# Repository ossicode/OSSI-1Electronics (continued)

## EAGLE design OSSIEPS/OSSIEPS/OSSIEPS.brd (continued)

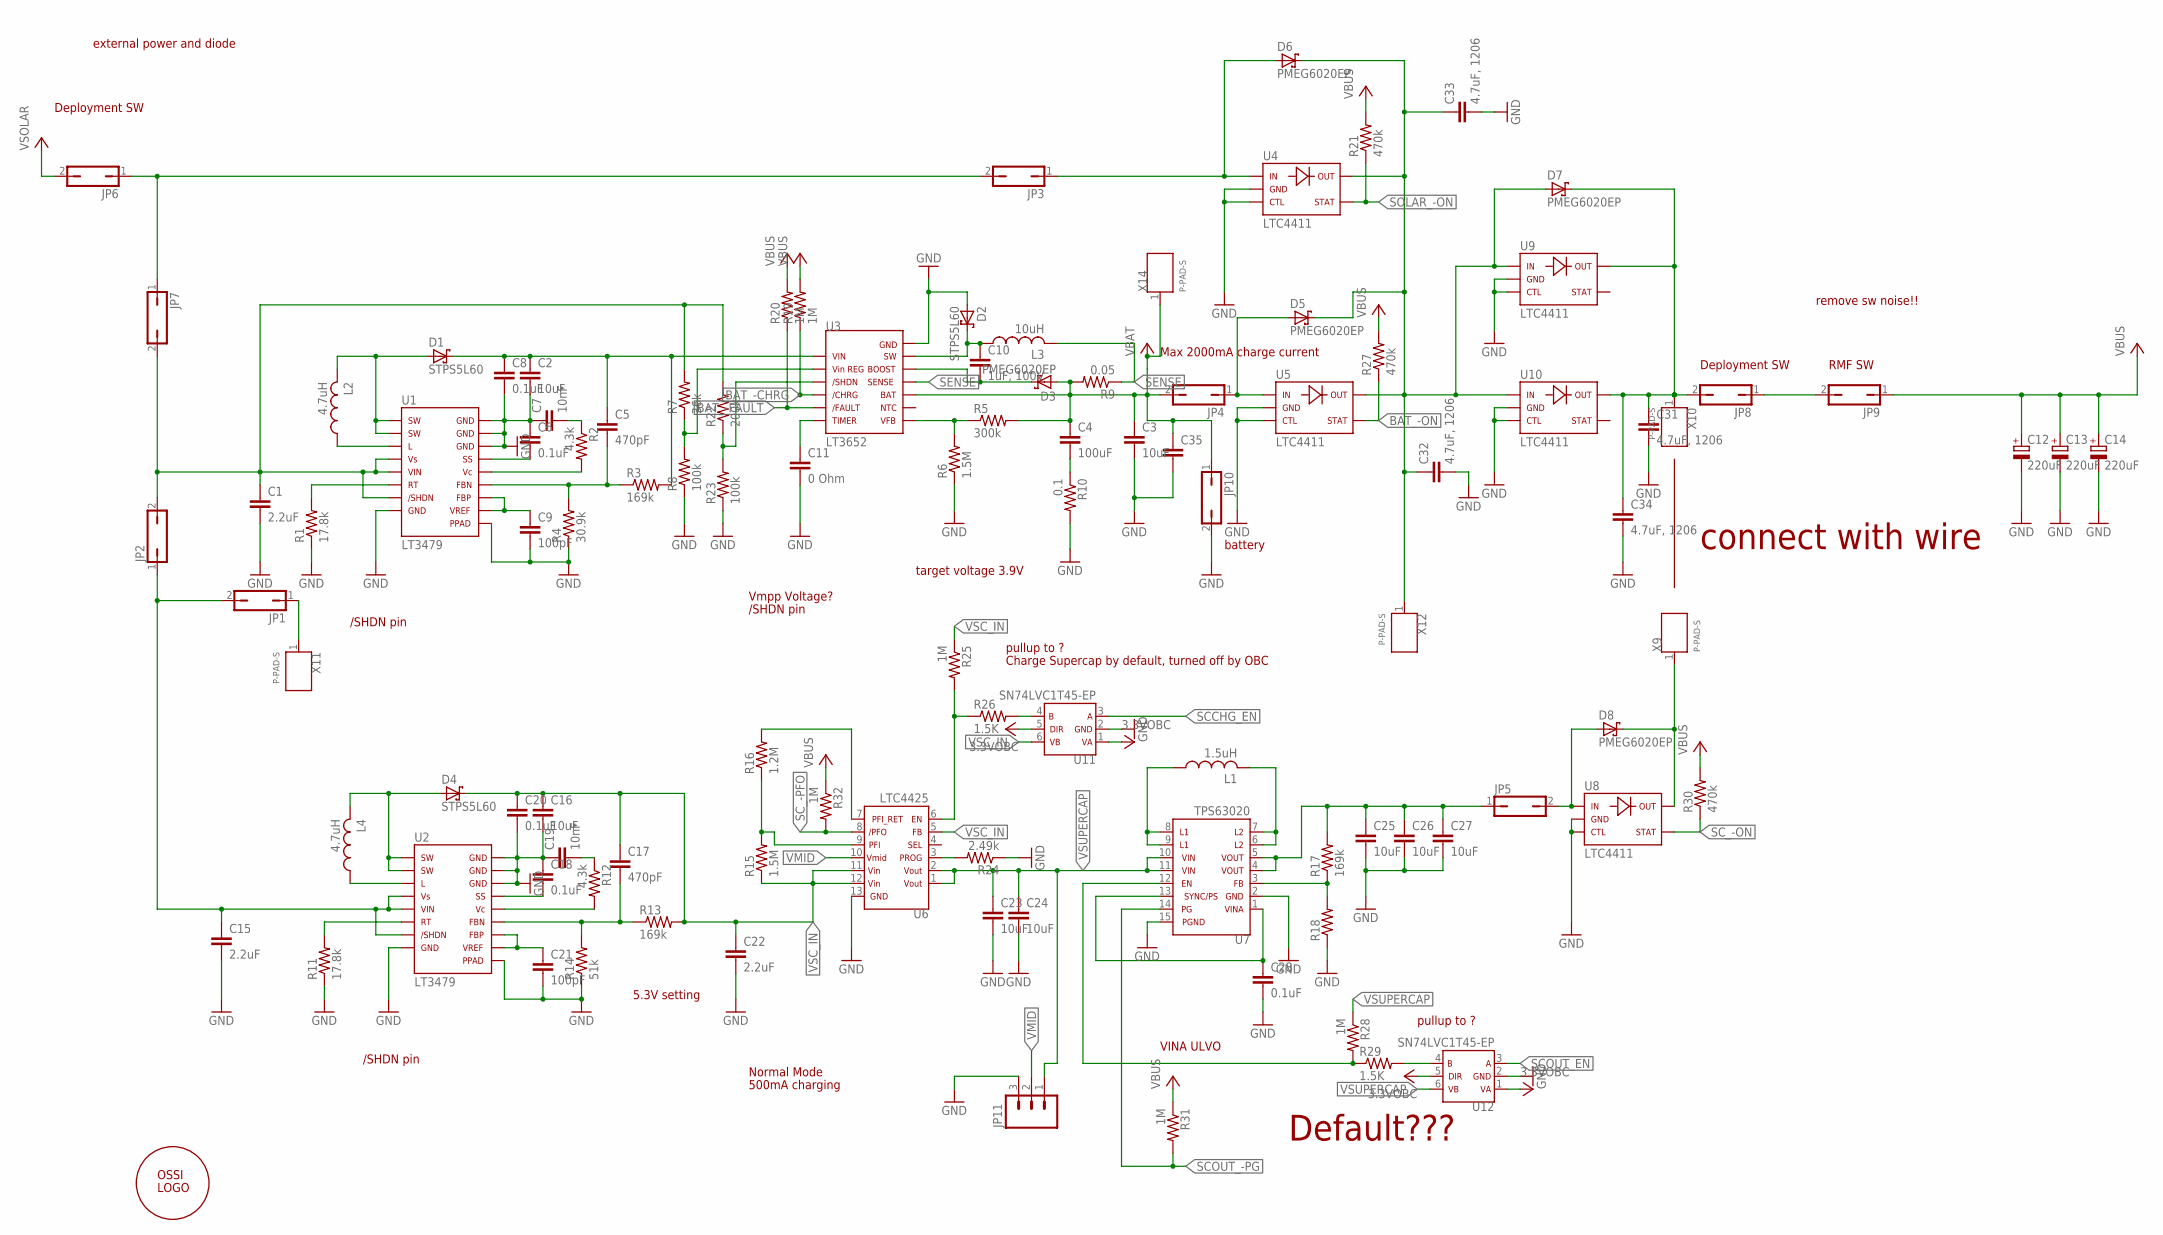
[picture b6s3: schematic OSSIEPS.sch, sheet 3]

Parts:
C1, C15, C22: 2.2uF; C1206-GCM31
C2, C3, C16, C23, C24, C25, C26, C27: 10uF; C1210-GCM32
C4: 100uF; C1210-TMK325
C5, C17: 470pF; C0603(1608)
C6, C8, C18, C20, C28: 0.1uF; C0603(1608)
C7, C19: 10nF; C0603(1608)
C9, C21: 100pF; C0603(1608)
C10: 1uF, 100V; C0805(2012)
C11: 0 Ohm; C0603(1608)
C12, C13, C14: 220uF; C2917(7343)-Y
C31, C32, C33, C34: 4.7uF, 1206; C1206-GCM31
C35: C0603(1608)
D1, D2, D4: STPS5L60
D3, D5, D6, D7, D8: PMEG6020EP
JP1, JP2, JP3, JP4, JP5, JP6, JP7, JP8, JP9, JP10: JP1Q; JP1
JP11: M03POLAR; MOLEX-1X3
L1: 1.5uH; L(4040)
L2, L4: 4.7uH; RLF7030
L3: 10uH; RLF12545
R1, R11: 17.8k; R0603(1608)
R2, R12: 4.3k; R0603(1608)
R3, R13, R17: 169k; R0603(1608)
R4: 30.9k; R0603(1608)
R5: 300k; R0603(1608)
R6, R15: 1.5M; R0603(1608)
R7: 36k; R0603(1608)
R8, R23: 100k; R0603(1608)
R9: 0.05; WSL1206
R10: 0.1; WSL1206
R14: 51k; R0603(1608)
R16: 1.2M; R0603(1608)
R18: R0603(1608)
R19, R20, R25, R28, R31, R32: 1M; R0603(1608)
R21, R27, R30: 470k; R0603(1608)
R22: 200k; R0603(1608)
R24: 2.49k; R0603(1608)
R26, R29: 1.5K; R0603(1608)
U1, U2: LT3479; TSSOP16-FE
U3: LT3652; MSE
U4, U5, U8, U9, U10: LTC4411; TSOT23-5
U6: LTC4425; MSE
U7: TPS63020; VSON-14
U11, U12: SN74LVC1T45-EP; SOT-6DCK
U$1: OSSILOGORECT; OSSILOGORECT1005
X9, X10, X11, X12, X14: P-PAD-S

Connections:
3.3VOBC: U11.1, U11.5, U12.1, U12.5; also elsewhere on the board
BAT_-CHRG: R19.1, U3.4; also elsewhere on the board
BAT_-FAULT: R20.1, U3.5; also elsewhere on the board
BAT_-ON: R27.1, U5.P$4; also elsewhere on the board
GND: C1.P$2 (2), C2.P$2 (2), C3.P$2 (2), C6.1, C7.1, C8.2, C9.2, C11.2, C12.2 (-), C13.2 (-), C14.2 (-), C15.P$2 (2), C16.P$2 (2), C18.1, C19.1, C20.2, C21.2, C22.P$2 (2), C23.P$2 (2), C24.P$2 (2), C25.P$2 (2), C26.P$2 (2), C27.P$2 (2), C28.2, C31.P$2 (2), C32.P$2 (2), C33.P$2 (2), C34.P$2 (2), C35.2, D2.A, JP10.2, JP11.3, R1.1, R4.1, R6.1, R8.1, R10.P$2 (2), R11.1, R14.1, R18.1, R23.1, R24.1, U1.8, U1.14, U1.15, U1.16, U1.PPAD, U2.8, U2.14, U2.15, U2.16, U2.PPAD, U3.13, U4.P$2, U4.P$3, U5.P$2, U5.P$3, U6.13, U7.2 (GND), U7.15 (PGND), U8.P$2, U8.P$3, U9.P$2, U9.P$3, U10.P$2, U10.P$3, U11.2, U12.2; also elsewhere on the board
unnamed: L2.P$1 (1), U1.3
unnamed: R7.1, R8.2, U3.2
unnamed: C2.P$1 (1), C5.1, C8.1, D1.C, R3.2, U3.1
unnamed: C4.P$2 (2), R10.P$1 (1)
unnamed: C6.2, U1.13
unnamed: D1.A, L2.P$2 (2), U1.1, U1.2
unnamed: C7.2, R2.1
unnamed: R2.2, U1.12
unnamed: C5.2, R3.1, R4.2, U1.11
unnamed: C9.1, U1.9, U1.10
unnamed: R1.2, U1.6
unnamed: R22.1, R23.2, U3.3
unnamed: C10.2, D3.C, U3.11
unnamed: D8.C, U8.P$5, X9.1
unnamed: L4.P$1 (1), U2.3
unnamed: C10.1, D2.C, L3.P$1 (1), U3.12
unnamed: R5.1, R6.2, U3.7
unnamed: C32.P$1 (1), C33.P$1 (1), D5.C, D6.C, D7.A, U4.P$5, U5.P$5, U9.P$1, U10.P$1, X12.1
unnamed: C11.1, U3.6
unnamed: R26.2, U11.4
unnamed: C18.2, U2.13
unnamed: D4.A, L4.P$2 (2), U2.1, U2.2
unnamed: C19.2, R12.1
unnamed: R12.2, U2.12
unnamed: C17.2, R13.1, R14.2, U2.11
unnamed: C21.1, U2.9, U2.10
unnamed: R11.2, U2.6
unnamed: C15.P$1 (1), JP1.2, JP2.1, U2.4, U2.5, U2.7
unnamed: R15.2, R16.1, U6.9
unnamed: L1.1, U7.8 (L1), U7.9 (L1_2)
unnamed: R16.2, U6.7
unnamed: L1.2, U7.6 (L2), U7.7 (L2_2)
unnamed: C25.P$1 (1), C26.P$1 (1), C27.P$1 (1), JP5.1, R17.2, U7.4 (VOUT), U7.5 (VOUT2)
unnamed: R17.1, R18.2, U7.3 (FB)
unnamed: C28.1, U7.1 (VINA), U7.13 (SYNC/PS)
unnamed: D6.A, JP3.1, U4.P$1
unnamed: R24.2, U6.3
unnamed: R28.2, R29.1, U7.12 (EN)
unnamed: D5.A, JP4.1, U5.P$1
unnamed: D8.A, JP5.2, U8.P$1
unnamed: C1.P$1 (1), JP2.2, JP7.2, R7.2, R22.2, U1.4, U1.5, U1.7
unnamed: R25.2, R26.1, U6.6
unnamed: JP3.2, JP6.1, JP7.1
unnamed: C31.P$1 (1), C34.P$1 (1), D7.C, JP8.2, U9.P$5, U10.P$5, X10.1
unnamed: R29.2, U12.4
unnamed: JP8.1, JP9.2
unnamed: JP1.1, X11.1
SCCHG_EN: U11.3; also elsewhere on the board
SCOUT_-PG: R31.2, U7.14 (PG); also elsewhere on the board
SCOUT_EN: U12.3; also elsewhere on the board
SC_-ON: R30.1, U8.P$4; also elsewhere on the board
SC_-PFO: R32.2, U6.8; also elsewhere on the board
SENSE: L3.P$2 (2), R9.P$1 (1), U3.10
SOLAR_-ON: R21.1, U4.P$4; also elsewhere on the board
VBAT: C3.P$1 (1), C4.P$1 (1), C35.1, D3.A, JP4.2, JP10.1, R5.2, R9.P$2 (2), U3.9, X14.1; also elsewhere on the board
VBUS: C12.1 (+), C13.1 (+), C14.1 (+), JP9.1, R19.2, R20.2, R21.2, R27.2, R30.2, R31.1, R32.1; also elsewhere on the board
VMID: JP11.2, U6.10
VSC_IN: C16.P$1 (1), C17.1, C20.1, C22.P$1 (1), D4.C, R13.2, R15.1, R25.1, U6.5, U6.11, U6.12, U11.6
VSOLAR: JP6.2; also elsewhere on the board
VSUPERCAP: C23.P$1 (1), C24.P$1 (1), JP11.1, R28.1, U6.1, U6.2, U7.10 (VIN), U7.11 (VIN2), U12.6; also elsewhere on the board

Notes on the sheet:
/SHDN pin
5.3V setting
VINA ULVO
Normal Mode
500mA charging
Charge Supercap by default, turned off by OBC
Vmpp Voltage?
Max 2000mA charge current
target voltage 3.9V
Deployment SW
RMF SW
external power and diode
pullup to ?
remove sw noise!!
battery
Default???
connect with wire

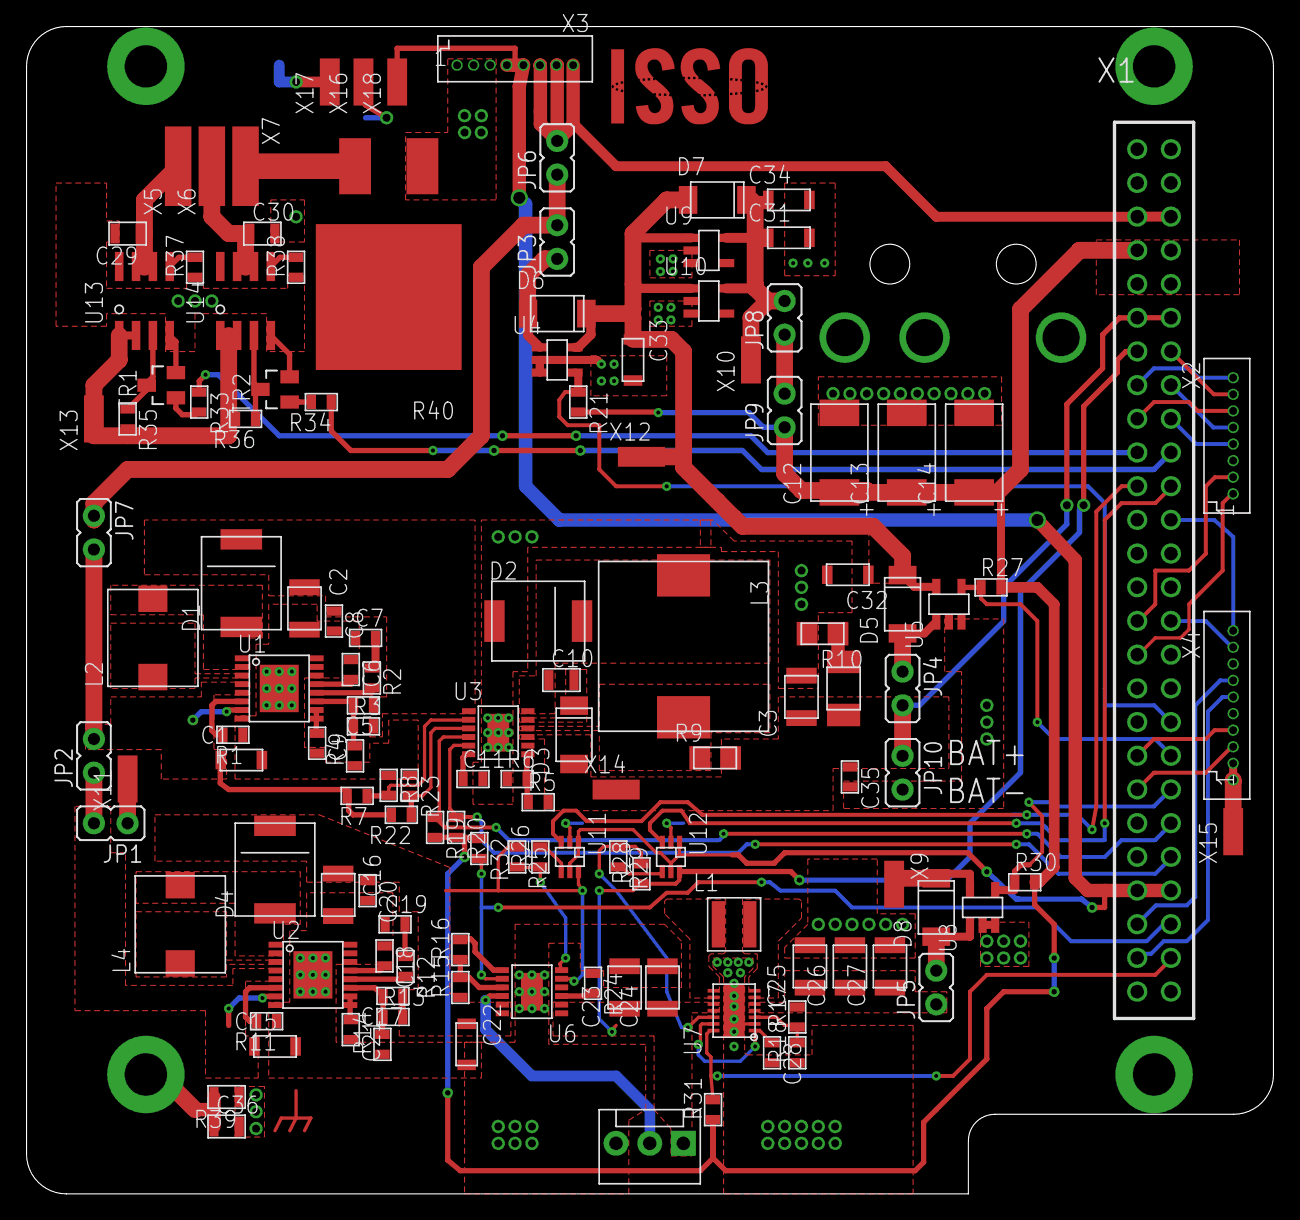
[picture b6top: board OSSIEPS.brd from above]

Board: 2 copper layers, 94.0 x 88.0 mm, 138 parts (1 on the bottom side), 91 nets.

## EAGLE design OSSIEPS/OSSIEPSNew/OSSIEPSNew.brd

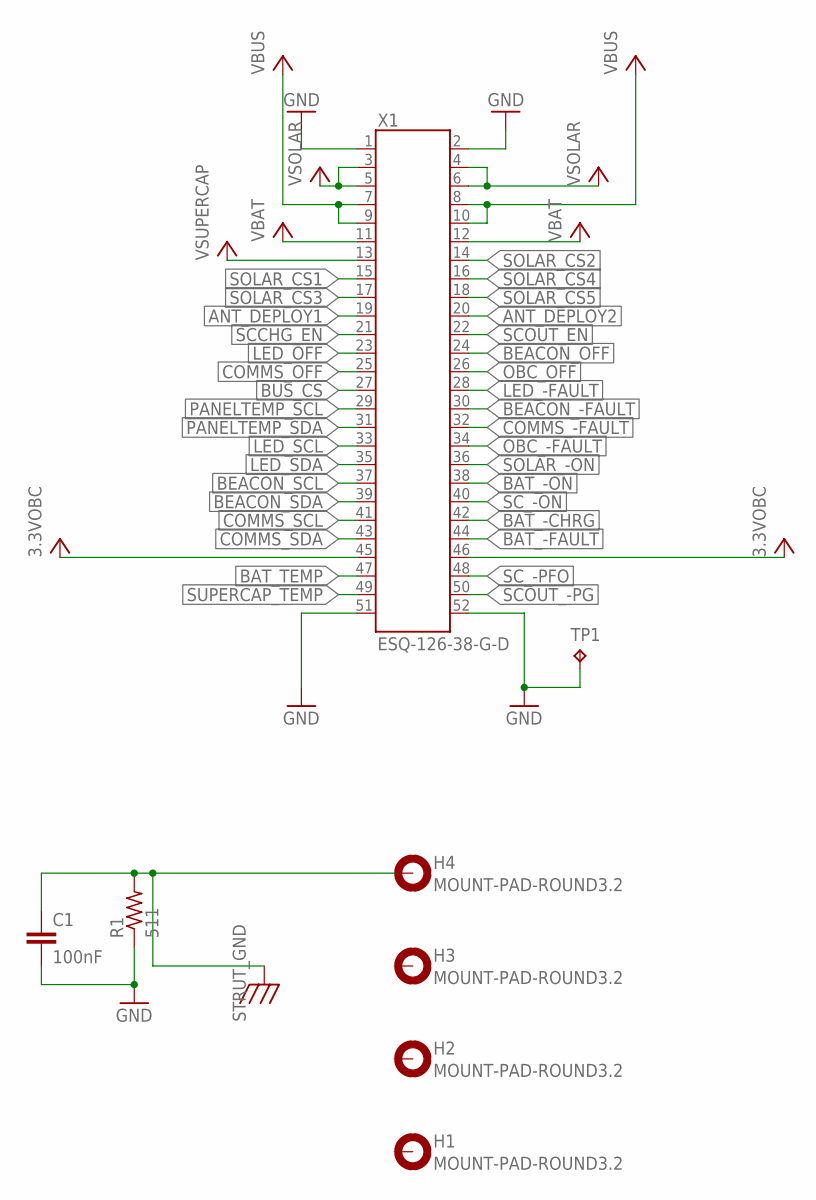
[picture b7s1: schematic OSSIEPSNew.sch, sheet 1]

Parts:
C1: 100nF; C0805(2012)
H1, H2, H3, H4: MOUNT-PAD-ROUND3.2; 3.2-PAD-ROUND
R1: 511; WSL1206
TP1: TP; TP-13
X1: ESQ-126-38-G-D; ESQ-126-XX-X-D

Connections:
3.3VOBC: X1.45, X1.46; also elsewhere on the board
ANT_DEPLOY1: X1.19; also elsewhere on the board
ANT_DEPLOY2: X1.20; also elsewhere on the board
BAT_-CHRG: X1.42; also elsewhere on the board
BAT_-FAULT: X1.44; also elsewhere on the board
BAT_-ON: X1.38; also elsewhere on the board
BAT_TEMP: X1.47
BEACON_-FAULT: X1.30
BEACON_OFF: X1.24
BEACON_SCL: X1.37
BEACON_SDA: X1.39
BUS_CS: X1.27; also elsewhere on the board
COMMS_-FAULT: X1.32
COMMS_OFF: X1.25
COMMS_SCL: X1.41
COMMS_SDA: X1.43
GND: C1.2, R1.P$1 (1), TP1.TP, X1.1, X1.2, X1.51, X1.52; also elsewhere on the board
LED_-FAULT: X1.28
LED_OFF: X1.23
LED_SCL: X1.33
LED_SDA: X1.35
OBC_-FAULT: X1.34
OBC_OFF: X1.26
PANELTEMP_SCL: X1.29
PANELTEMP_SDA: X1.31
SCCHG_EN: X1.21; also elsewhere on the board
SCOUT_-PG: X1.50
SCOUT_EN: X1.22; also elsewhere on the board
SC_-ON: X1.40; also elsewhere on the board
SC_-PFO: X1.48; also elsewhere on the board
SOLAR_-ON: X1.36; also elsewhere on the board
SOLAR_CS1: X1.15
SOLAR_CS2: X1.14
SOLAR_CS3: X1.17
SOLAR_CS4: X1.16
SOLAR_CS5: X1.18
STRUT_GND: C1.1, H4.B3,2, R1.P$2 (2)
SUPERCAP_TEMP: X1.49
VBAT: X1.11, X1.12; also elsewhere on the board
VBUS: X1.7, X1.8, X1.9, X1.10; also elsewhere on the board
VSOLAR: X1.3, X1.4, X1.5, X1.6; also elsewhere on the board
VSUPERCAP: X1.13; also elsewhere on the board

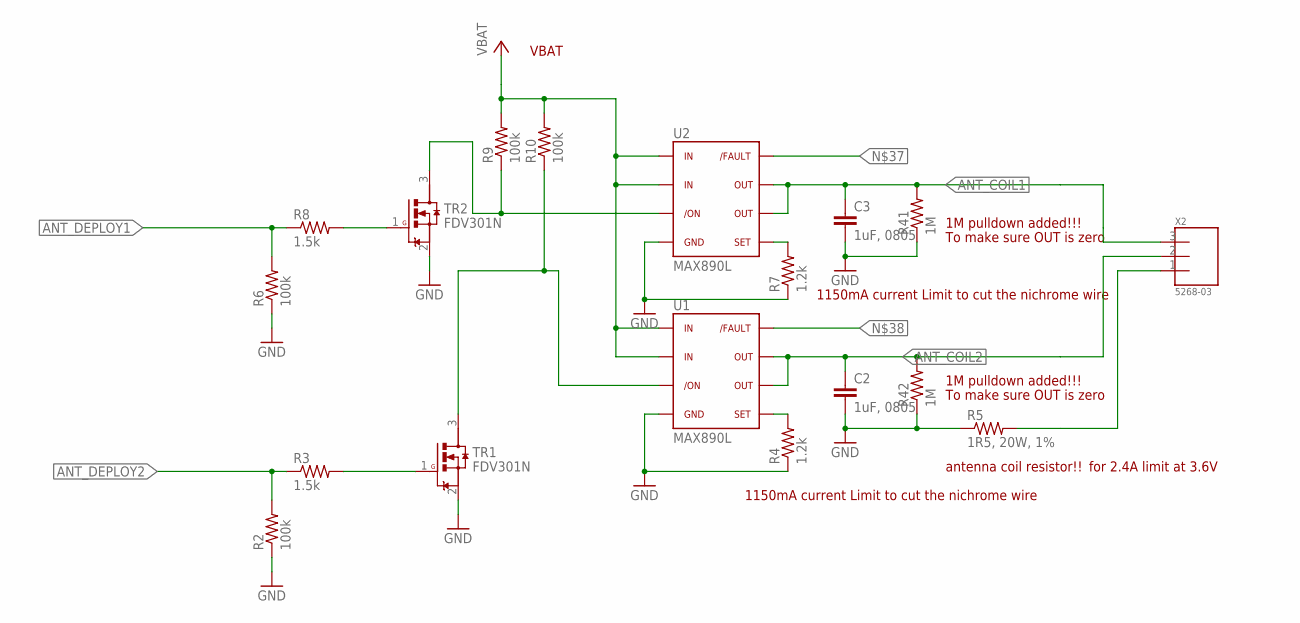
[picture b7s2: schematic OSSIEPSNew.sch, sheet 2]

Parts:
C2, C3: 1uF, 0805; C0805(2012)
R2, R6, R9, R10: 100k; R0603(1608)
R3, R8: 1.5k; R0603(1608)
R4, R7: 1.2k; R0603(1608)
R5: 1R5, 20W, 1%; PWR263S-20
R41, R42: 1M; R0603(1608)
TR1, TR2: FDV301N; SOT23
U1, U2: MAX890L; SO8
X2: 5268-03

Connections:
ANT_COIL1: C3.1, R41.2, U2.6, U2.7, X2.3
ANT_COIL2: C2.1, R42.2, U1.6, U1.7, X2.2
ANT_DEPLOY1: R6.2, R8.1; also elsewhere on the board
ANT_DEPLOY2: R2.2, R3.1; also elsewhere on the board
GND: C2.2, C3.2, R2.1, R4.1, R5.P$1 (1), R6.1, R7.1, R41.1, R42.1, TR1.2 (S), TR2.2 (S), U1.4, U2.4; also elsewhere on the board
unnamed: R3.2, TR1.1 (G)
unnamed: R8.2, TR2.1 (G)
unnamed: R9.1, TR2.3 (D), U2.3
unnamed: R10.1, TR1.3 (D), U1.3
unnamed: R7.2, U2.5
unnamed: R4.2, U1.5
unnamed: R5.P$2 (2), X2.1
VBAT: R9.2, R10.2, U1.1, U1.2, U2.1, U2.2; also elsewhere on the board

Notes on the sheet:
VBAT
antenna coil resistor!!
1150mA current Limit to cut the nichrome wire
for 2.4A limit at 3.6V
1M pulldown added!!!
To make sure OUT is zero

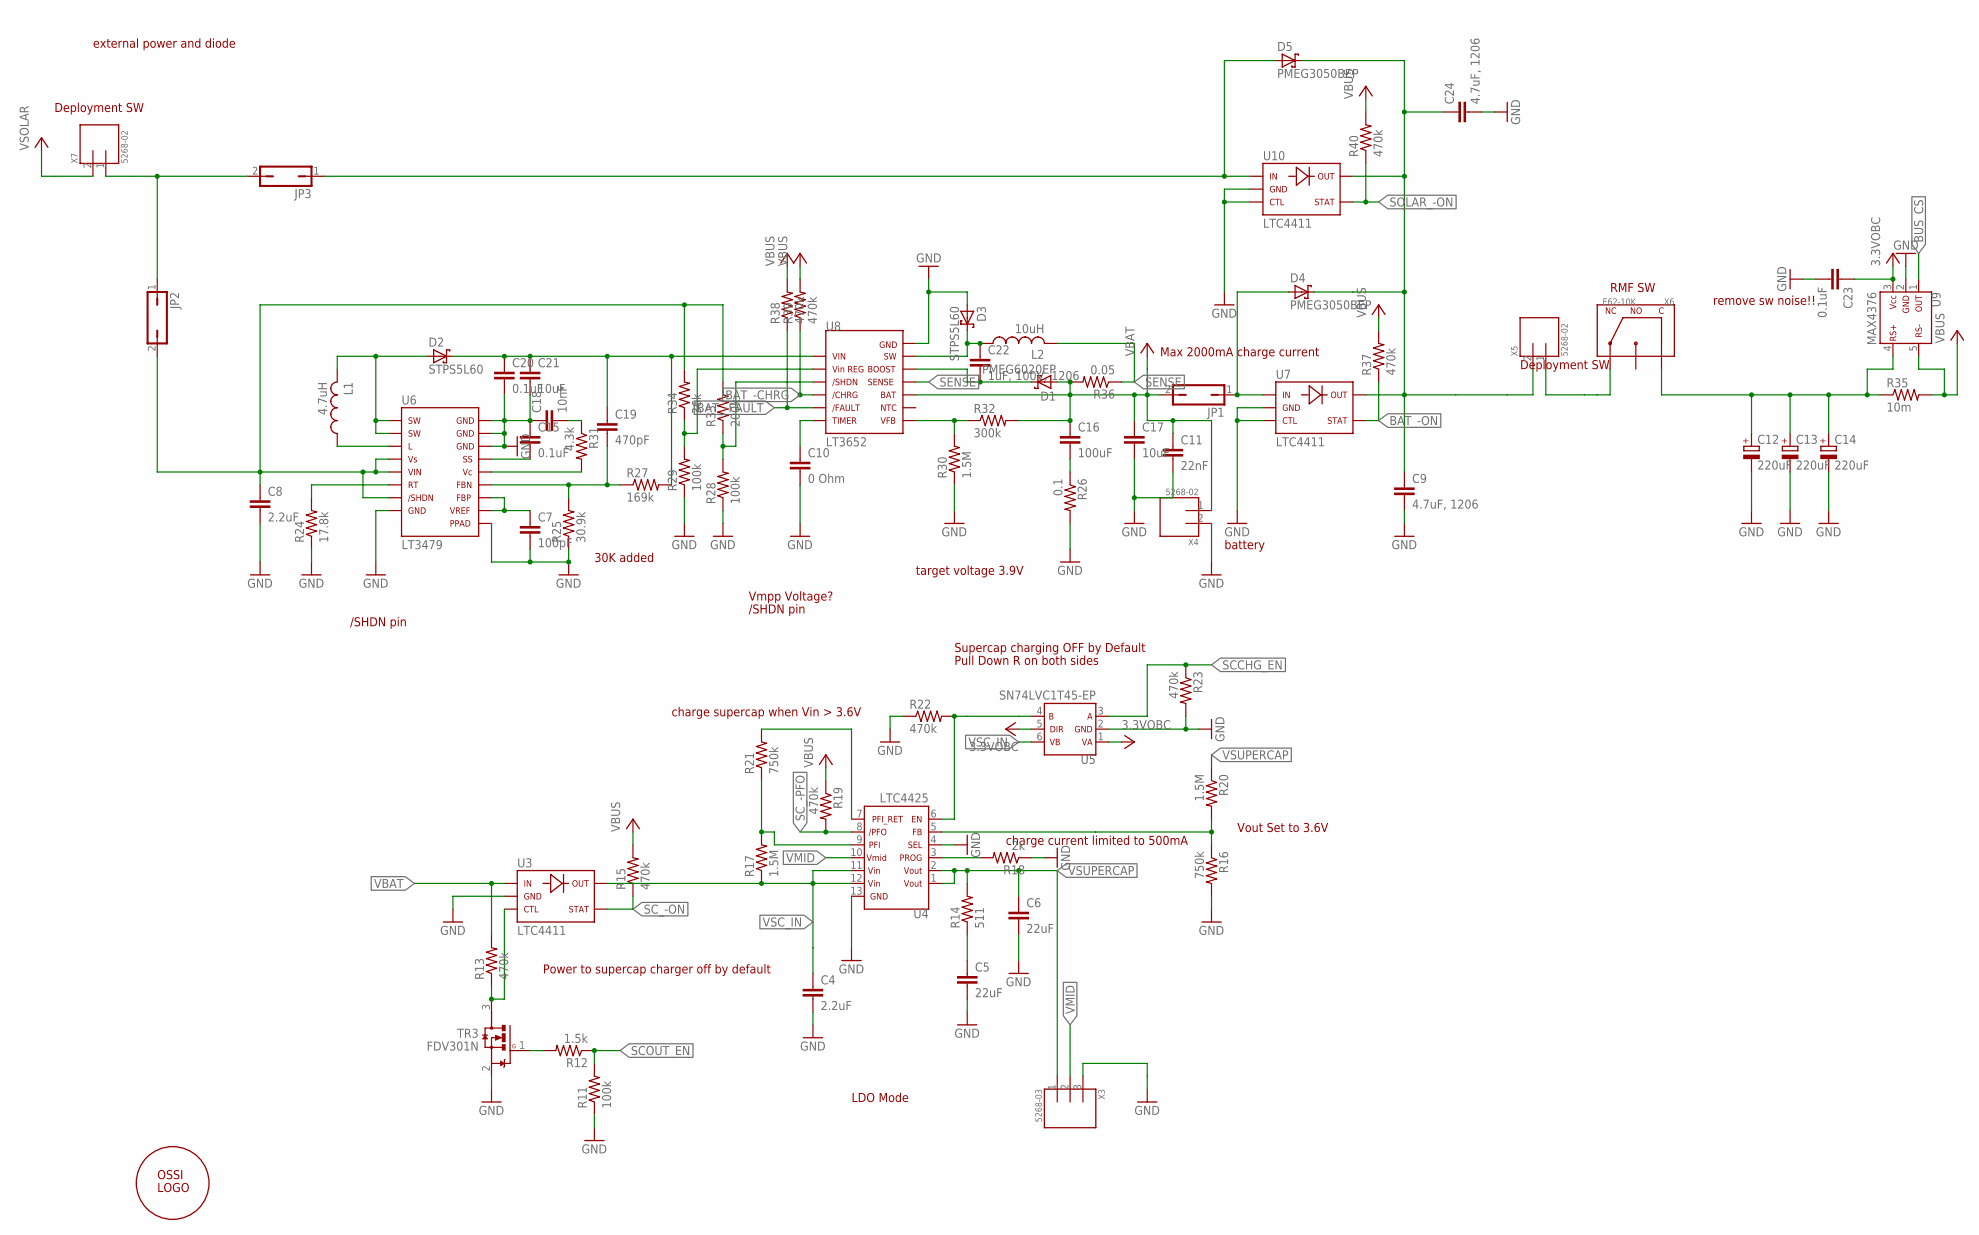
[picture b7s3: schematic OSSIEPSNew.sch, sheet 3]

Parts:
C4, C8: 2.2uF; C1206-GCM31
C5, C6: 22uF; C1210-GCM32
C7: 100pF; C0603(1608)
C9, C24: 4.7uF, 1206; C1206-GCM31
C10: 0 Ohm; C0603(1608)
C11: 22nF; C0603(1608)
C12, C13, C14: 220uF; C2917(7343)-Y
C15, C20, C23: 0.1uF; C0603(1608)
C16: 100uF; C1210-TMK325
C17, C21: 10uF; C1210-GCM32
C18: 10nF; C0603(1608)
C19: 470pF; C0603(1608)
C22: 1uF, 100V, 1206; C0805(2012)
D1: PMEG6020EP
D2, D3: STPS5L60
D4, D5: PMEG3050BEP; PMEG6020EP
JP1, JP2, JP3: JP1Q; JP1
L1: 4.7uH; RLF7030
L2: 10uH; RLF12545
R11, R28, R29: 100k; R0603(1608)
R12: 1.5k; R0603(1608)
R13, R15, R19, R22, R23, R37, R38, R39, R40: 470k; R0603(1608)
R14: 511; WSL1206
R16, R21: 750k; R0603(1608)
R17, R20, R30: 1.5M; R0603(1608)
R18: 2k; R0603(1608)
R24: 17.8k; R0603(1608)
R25: 30.9k; R0603(1608)
R26: 0.1; WSL1206
R27: 169k; R0603(1608)
R31: 4.3k; R0603(1608)
R32: 300k; R0603(1608)
R33: 200k; R0603(1608)
R34: 36k; R0603(1608)
R35: 10m; WSL1206
R36: 0.05; WSL1206
TR3: FDV301N; SOT23
U3, U7, U10: LTC4411; TSOT23-5
U4: LTC4425; MSE
U5: SN74LVC1T45-EP; SOT-6DCK
U6: LT3479; TSSOP16-FE
U8: LT3652; MSE
U9: MAX4376; SOT23-5DBV
U$1: OSSILOGORECT; OSSILOGORECT1005
X3: 5268-03
X4, X5, X7: 5268-02; 5628-02
X6: E62-10K

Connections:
3.3VOBC: C23.1, U5.1, U5.5, U9.3; also elsewhere on the board
BAT_-CHRG: R39.1, U8.4; also elsewhere on the board
BAT_-FAULT: R38.1, U8.5; also elsewhere on the board
BAT_-ON: R37.1, U7.P$4; also elsewhere on the board
BUS_CS: U9.1; also elsewhere on the board
GND: C4.P$2 (2), C5.P$2 (2), C6.P$2 (2), C7.2, C8.P$2 (2), C9.P$2 (2), C10.2, C11.2, C12.2 (-), C13.2 (-), C14.2 (-), C15.1, C17.P$2 (2), C18.1, C20.2, C21.P$2 (2), C23.2, C24.P$2 (2), D3.A, R11.1, R16.2, R18.1, R22.1, R23.2, R24.1, R25.1, R26.P$2 (2), R28.1, R29.1, R30.1, TR3.2 (S), U3.P$2, U4.4, U4.13, U5.2, U6.8, U6.14, U6.15, U6.16, U6.PPAD, U7.P$2, U7.P$3, U8.13, U9.2, U10.P$2, U10.P$3, X3.3, X4.2; also elsewhere on the board
unnamed: L1.P$1 (1), U6.3
unnamed: R29.2, R34.1, U8.2
unnamed: C19.1, C20.1, C21.P$1 (1), D2.C, R27.2, U8.1
unnamed: C16.P$2 (2), R26.P$1 (1)
unnamed: C15.2, U6.13
unnamed: D2.A, L1.P$2 (2), U6.1, U6.2
unnamed: C18.2, R31.1
unnamed: R31.2, U6.12
unnamed: C19.2, R25.2, R27.1, U6.11
unnamed: C7.1, U6.9, U6.10
unnamed: R24.2, U6.6
unnamed: R28.2, R33.1, U8.3
unnamed: C22.2, D1.C, U8.11
unnamed: R16.1, R20.2, U4.5
unnamed: C22.1, D3.C, L2.P$1 (1), U8.12
unnamed: R30.2, R32.1, U8.7
unnamed: C9.P$1 (1), C24.P$1 (1), D4.C, D5.C, U7.P$5, U10.P$5, X5.2
unnamed: C10.1, U8.6
unnamed: R22.2, U4.6, U5.4
unnamed: C5.P$1 (1), R14.P$1 (1)
unnamed: R13.1, TR3.3 (D), U3.P$3
unnamed: R12.2, TR3.1 (G)
unnamed: C12.1 (+), C13.1 (+), C14.1 (+), R35.P$1 (1), U9.4, X6.C
unnamed: R17.2, R21.1, U4.9
unnamed: R21.2, U4.7
unnamed: D5.A, JP3.1, U10.P$1
unnamed: R18.2, U4.3
unnamed: D4.A, JP1.1, U7.P$1
unnamed: C8.P$1 (1), JP2.2, R33.2, R34.2, U6.4, U6.5, U6.7
unnamed: JP2.1, JP3.2, X7.1
unnamed: X5.1, X6.NC
SCCHG_EN: R23.1, U5.3; also elsewhere on the board
SCOUT_EN: R11.2, R12.1; also elsewhere on the board
SC_-ON: R15.1, U3.P$4; also elsewhere on the board
SC_-PFO: R19.2, U4.8; also elsewhere on the board
SENSE: L2.P$2 (2), R36.P$1 (1), U8.10
SOLAR_-ON: R40.1, U10.P$4; also elsewhere on the board
VBAT: C11.1, C16.P$1 (1), C17.P$1 (1), D1.A, JP1.2, R13.2, R32.2, R36.P$2 (2), U3.P$1, U8.9, X4.1; also elsewhere on the board
VBUS: R15.2, R19.1, R35.P$2 (2), R37.2, R38.2, R39.2, R40.2, U9.5; also elsewhere on the board
VMID: U4.10, X3.2
VSC_IN: C4.P$1 (1), R17.1, U3.P$5, U4.11, U4.12, U5.6
VSOLAR: X7.2; also elsewhere on the board
VSUPERCAP: C6.P$1 (1), R14.P$2 (2), R20.1, U4.1, U4.2, X3.1; also elsewhere on the board

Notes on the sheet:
/SHDN pin
Vmpp Voltage?
Max 2000mA charge current
target voltage 3.9V
Deployment SW
RMF SW
external power and diode
remove sw noise!!
battery
LDO Mode
Vout Set to 3.6V
Supercap charging OFF by Default
Pull Down R on both sides
charge current limited to 500mA
charge supercap when Vin > 3.6V
Power to supercap charger off by default
30K added

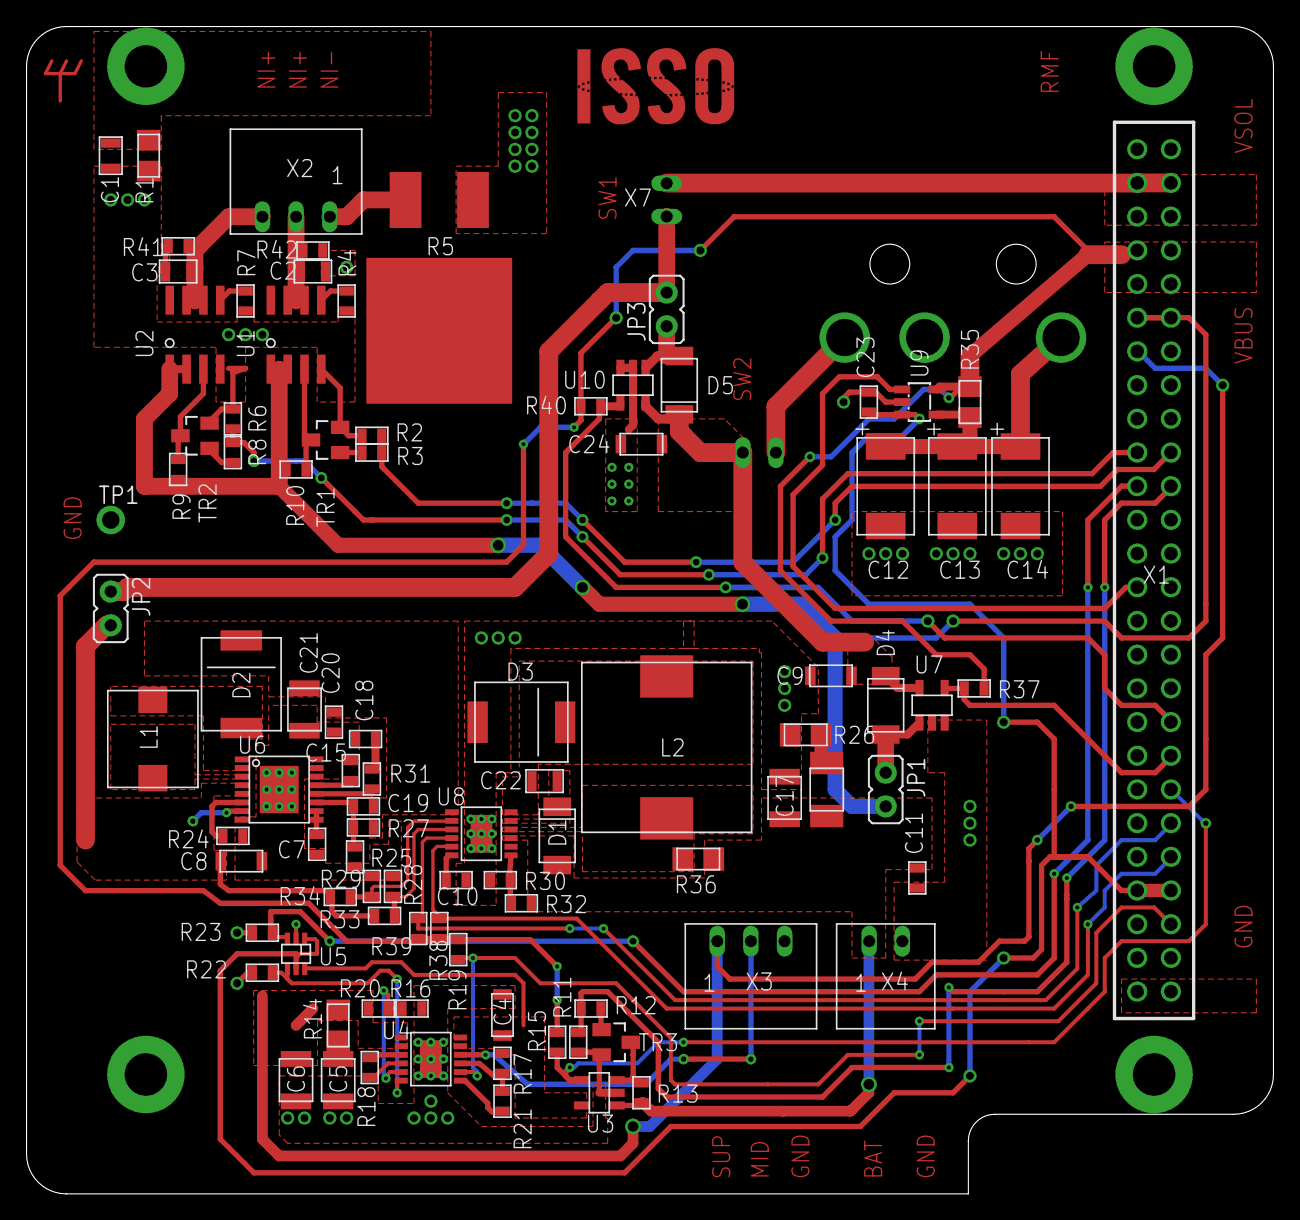
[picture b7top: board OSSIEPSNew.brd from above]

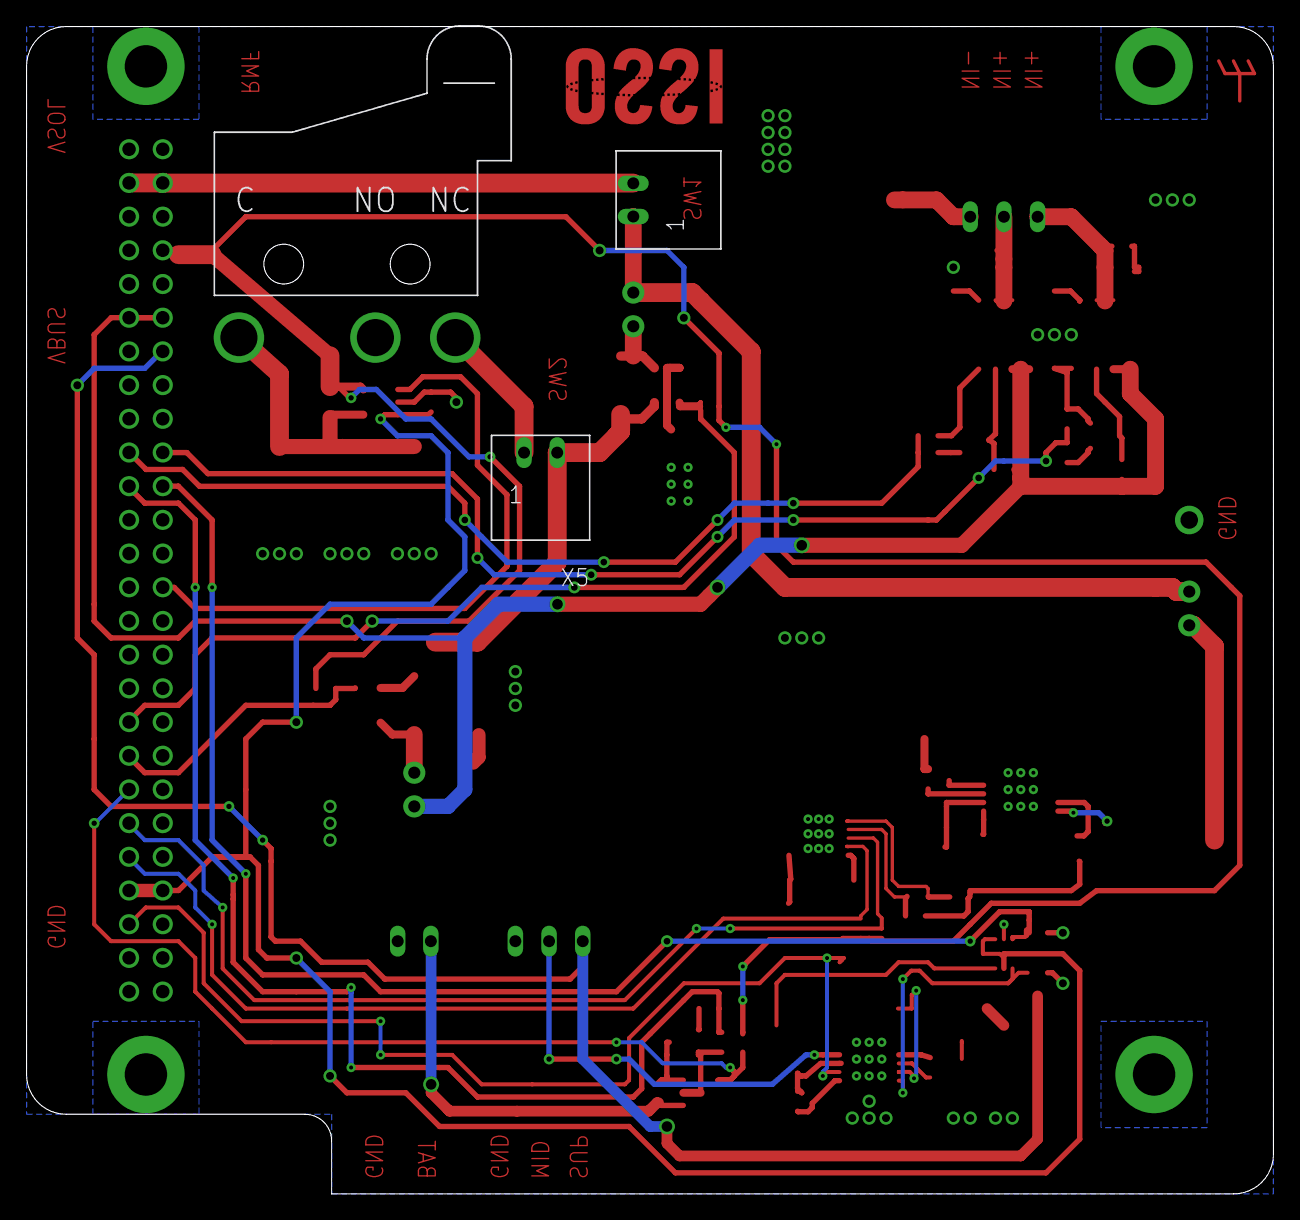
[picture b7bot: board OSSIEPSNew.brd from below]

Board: 2 copper layers, 94.0 x 88.0 mm, 102 parts (3 on the bottom side), 61 nets.

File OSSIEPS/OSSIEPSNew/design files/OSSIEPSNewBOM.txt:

Part	Value	Attributes	Package	Description	Part Num
C1	100nF		C0805(2012)		*
H1	MOUNT-PAD-ROUND3.2		3.2-PAD-ROUND		*
H2	MOUNT-PAD-ROUND3.2		3.2-PAD-ROUND		*
H3	MOUNT-PAD-ROUND3.2		3.2-PAD-ROUND		*
H4	MOUNT-PAD-ROUND3.2		3.2-PAD-ROUND		*
R1	511		WSL1206		*
TP1	TP		TP-13		*
X1	ESQ-126-38-G-D		ESQ-126-XX-X-D	Samtec ESQ-126-XX-G-D Elevated Sockets Seires	*
C2	1uF, 0805		C0805(2012)		*
C3	1uF, 0805		C0805(2012)		*
R2	100k		R0603(1608)		*
R3	1.5k		R0603(1608)		*
R4	1.2k		R0603(1608)		*
R5	1R5, 20W, 1%		PWR263S-20		*
R6	100k		R0603(1608)		*
R7	1.2k		R0603(1608)		*
R8	1.5k		R0603(1608)		*
R9	100k		R0603(1608)		*
R10	100k		R0603(1608)		*
R41	1M		R0603(1608)		*
R42	1M		R0603(1608)		*
TR1	FDV301N		SOT23	FDV301N Digital N channel - FET / Rdson = 5 Ohm / Vgs = 0.7~1.06V / Ids = 220mA	*
TR2	FDV301N		SOT23	FDV301N Digital N channel - FET / Rdson = 5 Ohm / Vgs = 0.7~1.06V / Ids = 220mA	*
U1	MAX890L		SO8	MAX 890L	*
U2	MAX890L		SO8	MAX 890L	*
X2	5268-03		5268-03		*
C4	2.2uF		C1206-GCM31		*
C5	22uF		C1210-GCM32		*
C6	22uF		C1210-GCM32		*
C7	100pF		C0603(1608)		*
C8	2.2uF		C1206-GCM31		*
C9	4.7uF, 1206		C1206-GCM31		*
C10	0 Ohm		C0603(1608)		*
C11	22nF		C0603(1608)		*
C12	220uF		C2917(7343)-Y	TAJY227K010RNJ	*
C13	220uF		C2917(7343)-Y	TAJY227K010RNJ	*
C14	220uF		C2917(7343)-Y	TAJY227K010RNJ	*
C15	0.1uF		C0603(1608)		*
C16	100uF		C1210-TMK325		*
C17	10uF		C1210-GCM32		*
C18	10nF		C0603(1608)		*
C19	470pF		C0603(1608)		*
C20	0.1uF		C0603(1608)		*
C21	10uF		C1210-GCM32		*
C22	1uF, 100V, 1206		C0805(2012)		*
C23	0.1uF		C0603(1608)		*
C24	4.7uF, 1206		C1206-GCM31		*
D1	PMEG6020EP		PMEG6020EP		*
D2	STPS5L60		STPS5L60	STPS5L60	*
D3	STPS5L60		STPS5L60	STPS5L60	*
D4	PMEG3050BEP		PMEG6020EP		*
D5	PMEG3050BEP		PMEG6020EP		*
JP1			JP1	JUMPER	*
JP2			JP1	JUMPER	*
JP3			JP1	JUMPER	*
L1	4.7uH		RLF7030		*
L2	10uH		RLF12545		*
R11	100k		R0603(1608)		*
R12	1.5k		R0603(1608)		*
R13	470k		R0603(1608)		*
R14	511		WSL1206		*
R15	470k		R0603(1608)		*
R16	750k		R0603(1608)		*
R17	1.5M		R0603(1608)		*
R18	2k		R0603(1608)		*
R19	470k		R0603(1608)		*
R20	1.5M		R0603(1608)		*
R21	750k		R0603(1608)		*
R22	470k		R0603(1608)		*
R23	470k		R0603(1608)		*
R24	17.8k		R0603(1608)		*
R25	30.9k		R0603(1608)		*
R26	0.1		WSL1206		*
R27	169k		R0603(1608)		*
R28	100k		R0603(1608)		*
R29	100k		R0603(1608)		*
R30	1.5M		R0603(1608)		*
R31	4.3k		R0603(1608)		*
R32	300k		R0603(1608)		*
R33	200k		R0603(1608)		*
R34	36k		R0603(1608)		*
R35	10m		WSL1206		*
R36	0.05		WSL1206		*
R37	470k		R0603(1608)		*
R38	470k		R0603(1608)		*
R39	470k		R0603(1608)		*
R40	470k		R0603(1608)		*
TR3	FDV301N		SOT23	FDV301N Digital N channel - FET / Rdson = 5 Ohm / Vgs = 0.7~1.06V / Ids = 220mA	*
U$1	OSSILOGORECT		OSSILOGORECT1005		*
U3	LTC4411		TSOT23-5	Linear Techonology LTC4411 ideal diode	*
U4	LTC4425		MSE	LTC4425 Linear SuperCap Charger With Current-Limited Ideal Diode and V/I Monitor	*
U5	SN74LVC1T45-EP		SOT-6DCK	SN74LVC1T45-EP	*
U6	LT3479		TSSOP16-FE	LT3479 inverting switching convertor	*
U7	LTC4411		TSOT23-5	Linear Techonology LTC4411 ideal diode	*
U8	LT3652		MSE	LT3652 Battery Charger	*
U9	MAX4376		SOT23-5DBV		*
U10	LTC4411		TSOT23-5	Linear Techonology LTC4411 ideal diode	*
X3	5268-03		5268-03		*
X4	5268-02		5628-02		*
X5	5268-02		5628-02		*
X6	E62-10K		E62-10K	Cherry E620-10K spdt sw for Remove Before Flight pin	*
X7	5268-02		5628-02		*
